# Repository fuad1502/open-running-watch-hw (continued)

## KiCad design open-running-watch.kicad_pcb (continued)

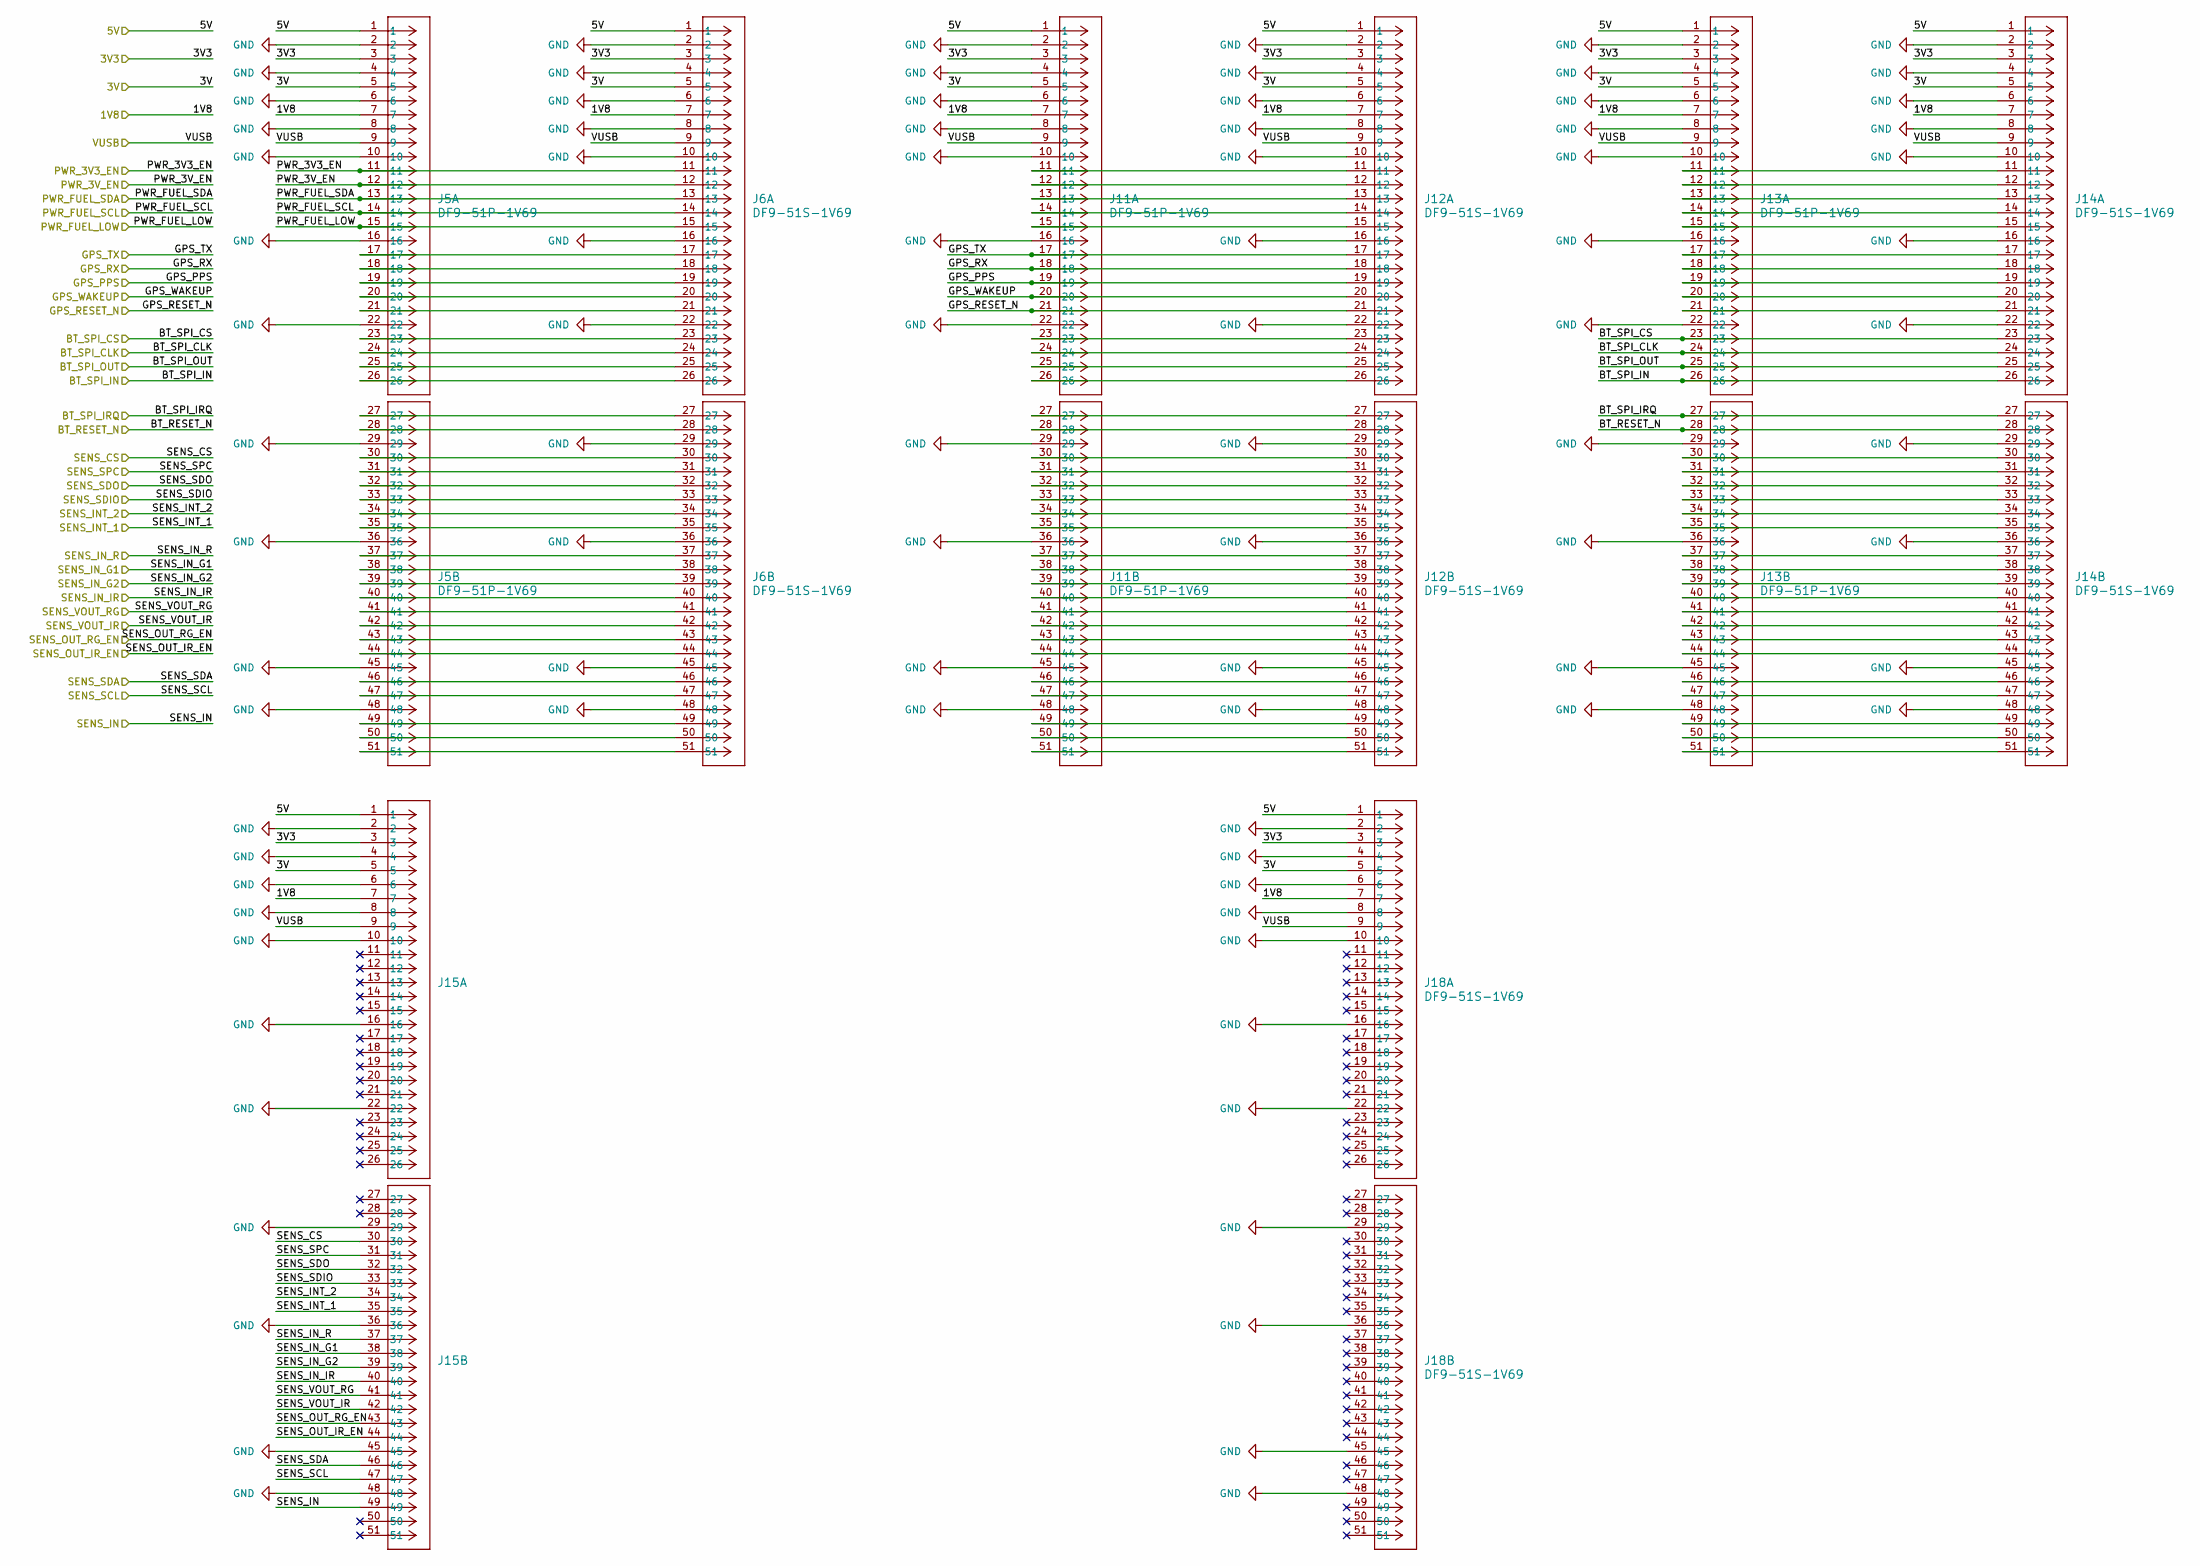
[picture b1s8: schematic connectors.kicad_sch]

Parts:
J5, J11, J13, J15: DF9-51P-1V69; CON9_1X51_MDZL_DF9_HIR
J6, J12, J14, J18: DF9-51S-1V69; CON9_1X51_DZL_DF9_HIR

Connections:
/1V8: J5.7, J6.7, J11.7, J12.7, J13.7, J14.7, J15.7, J18.7; also elsewhere on the board
/3V: J5.5, J6.5, J11.5, J12.5, J13.5, J14.5, J15.5, J18.5; also elsewhere on the board
/3V3: J5.3, J6.3, J11.3, J12.3, J13.3, J14.3, J15.3, J18.3; also elsewhere on the board
/5V: J5.1, J6.1, J11.1, J12.1, J13.1, J14.1, J15.1, J18.1; also elsewhere on the board
/BT_RESET_N: J13.28, J14.28; also elsewhere on the board
/BT_SPI_CLK: J13.24, J14.24; also elsewhere on the board
/BT_SPI_CS: J13.23, J14.23; also elsewhere on the board
/BT_SPI_IN: J13.26, J14.26; also elsewhere on the board
/BT_SPI_IRQ: J13.27, J14.27; also elsewhere on the board
/BT_SPI_OUT: J13.25, J14.25; also elsewhere on the board
/GPS_PPS: J11.19, J12.19; also elsewhere on the board
/GPS_RESET_N: J11.21, J12.21; also elsewhere on the board
/GPS_RX: J11.18, J12.18; also elsewhere on the board
/GPS_TX: J11.17, J12.17; also elsewhere on the board
/GPS_WAKEUP: J11.20, J12.20; also elsewhere on the board
/PWR_3V3_EN: J5.11, J6.11; also elsewhere on the board
/PWR_3V_EN: J5.12, J6.12; also elsewhere on the board
/PWR_FUEL_LOW: J5.15, J6.15; also elsewhere on the board
/PWR_FUEL_SCL: J5.14, J6.14; also elsewhere on the board
/PWR_FUEL_SDA: J5.13, J6.13; also elsewhere on the board
/SENS_CS: J15.30; also elsewhere on the board
/SENS_IN: J15.49; also elsewhere on the board
/SENS_INT_1: J15.35; also elsewhere on the board
/SENS_INT_2: J15.34; also elsewhere on the board
/SENS_IN_G1: J15.38; also elsewhere on the board
/SENS_IN_G2: J15.39; also elsewhere on the board
/SENS_IN_IR: J15.40; also elsewhere on the board
/SENS_IN_R: J15.37; also elsewhere on the board
/SENS_OUT_IR_EN: J15.44; also elsewhere on the board
/SENS_OUT_RG_EN: J15.43; also elsewhere on the board
/SENS_SCL: J15.47; also elsewhere on the board
/SENS_SDA: J15.46; also elsewhere on the board
/SENS_SDIO: J15.33; also elsewhere on the board
/SENS_SDO: J15.32; also elsewhere on the board
/SENS_SPC: J15.31; also elsewhere on the board
/SENS_VOUT_IR: J15.42; also elsewhere on the board
/SENS_VOUT_RG: J15.41; also elsewhere on the board
/VUSB: J5.9, J6.9, J11.9, J12.9, J13.9, J14.9, J15.9, J18.9; also elsewhere on the board
GND: J5.2, J5.4, J5.6, J5.8, J5.10, J5.16, J5.22, J5.29, J5.36, J5.45, J5.48, J6.2, J6.4, J6.6, J6.8, J6.10, J6.16, J6.22, J6.29, J6.36, J6.45, J6.48, J11.2, J11.4, J11.6, J11.8, J11.10, J11.16, J11.22, J11.29, J11.36, J11.45, J11.48, J12.2, J12.4, J12.6, J12.8, J12.10, J12.16, J12.22, J12.29, J12.36, J12.45, J12.48, J13.2, J13.4, J13.6, J13.8, J13.10, J13.16, J13.22, J13.29, J13.36, J13.45, J13.48, J14.2, J14.4, J14.6, J14.8, J14.10, J14.16, J14.22, J14.29, J14.36, J14.45, J14.48, J15.2, J15.4, J15.6, J15.8, J15.10, J15.16, J15.22, J15.29, J15.36, J15.45, J15.48, J18.2, J18.4, J18.6, J18.8, J18.10, J18.16, J18.22, J18.29, J18.36, J18.45, J18.48; also elsewhere on the board
unnamed: J5.17, J6.17
unnamed: J5.18, J6.18
unnamed: J5.19, J6.19
unnamed: J5.20, J6.20
unnamed: J5.21, J6.21
unnamed: J5.23, J6.23
unnamed: J5.24, J6.24
unnamed: J5.25, J6.25
unnamed: J5.26, J6.26
unnamed: J5.27, J6.27
unnamed: J5.28, J6.28
unnamed: J5.30, J6.30
unnamed: J5.31, J6.31
unnamed: J5.32, J6.32
unnamed: J5.33, J6.33
unnamed: J5.34, J6.34
unnamed: J5.35, J6.35
unnamed: J5.37, J6.37
unnamed: J5.38, J6.38
unnamed: J5.39, J6.39
unnamed: J5.40, J6.40
unnamed: J5.41, J6.41
unnamed: J5.42, J6.42
unnamed: J5.43, J6.43
unnamed: J5.44, J6.44
unnamed: J5.46, J6.46
unnamed: J5.47, J6.47
unnamed: J5.49, J6.49
unnamed: J5.50, J6.50
unnamed: J5.51, J6.51
unnamed: J11.11, J12.11
unnamed: J11.12, J12.12
unnamed: J11.13, J12.13
unnamed: J11.14, J12.14
unnamed: J11.15, J12.15
unnamed: J11.23, J12.23
unnamed: J11.24, J12.24
unnamed: J11.25, J12.25
unnamed: J11.26, J12.26
unnamed: J11.27, J12.27
unnamed: J11.28, J12.28
unnamed: J11.30, J12.30
unnamed: J11.31, J12.31
unnamed: J11.32, J12.32
unnamed: J11.33, J12.33
unnamed: J11.34, J12.34
unnamed: J11.35, J12.35
unnamed: J11.37, J12.37
unnamed: J11.38, J12.38
unnamed: J11.39, J12.39
unnamed: J11.40, J12.40
unnamed: J11.41, J12.41
unnamed: J11.42, J12.42
unnamed: J11.43, J12.43
unnamed: J11.44, J12.44
unnamed: J11.46, J12.46
unnamed: J11.47, J12.47
unnamed: J11.49, J12.49
unnamed: J11.50, J12.50
unnamed: J11.51, J12.51
unnamed: J13.11, J14.11
unnamed: J13.12, J14.12
unnamed: J13.13, J14.13
unnamed: J13.14, J14.14
unnamed: J13.15, J14.15
unnamed: J13.17, J14.17
unnamed: J13.18, J14.18
unnamed: J13.19, J14.19
unnamed: J13.20, J14.20
unnamed: J13.21, J14.21
unnamed: J13.30, J14.30
unnamed: J13.31, J14.31
unnamed: J13.32, J14.32
unnamed: J13.33, J14.33
unnamed: J13.34, J14.34
unnamed: J13.35, J14.35
unnamed: J13.37, J14.37
unnamed: J13.38, J14.38
unnamed: J13.39, J14.39
unnamed: J13.40, J14.40
unnamed: J13.41, J14.41
unnamed: J13.42, J14.42
unnamed: J13.43, J14.43
unnamed: J13.44, J14.44
unnamed: J13.46, J14.46
unnamed: J13.47, J14.47
unnamed: J13.49, J14.49
unnamed: J13.50, J14.50
unnamed: J13.51, J14.51

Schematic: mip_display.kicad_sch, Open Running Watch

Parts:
C79, C82, C85, C86: 1u; C_0603_1608Metric; Manufacturer_Part_Number C0603C105K4RACTU
C80, C81: 100n; C_0402_1005Metric; Manufacturer_Part_Number GRM155R71A104MA01D
C84: 560p; C_0402_1005Metric; Manufacturer_Part_Number GRT1555C1H561FA02D
IC21: LSF0204GU12X; Mouser Part Number 771-LSF0204GU12X
J3: 1-2328702-0; 123287020; Mouser Part Number 571-1-2328702-0
J4: 2328702-4; 23287024; Mouser Part Number 571-2328702-4
Q4: BC846; SOT-23; Manufacturer_Part_Number BC847BLT1G
R46: 10k; R_0402_1005Metric; Manufacturer_Part_Number RC0402JR-0710KP
R59, R62: 0; R_0402_1005Metric_Pad0.72x0.64mm_HandSolder; Manufacturer_Part_Number AC0402JR-7D0RL
R60, R61: 0; R_0402_1005Metric_Pad0.72x0.64mm_HandSolder; Manufacturer_Part_Number AC0402JR-7D0RL; not fitted

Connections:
/1V8: C81.2, C82.2, IC21.1 (REFA); also elsewhere on the board
/5V: C85.2, C86.2, J3.4, J3.5; also elsewhere on the board
/controller/CS3_1: IC21.3 (A2); also elsewhere on the board
/controller/DISP_EN: IC21.2 (A1); also elsewhere on the board
/controller/DISP_IO_EN: IC21.12 (EN); also elsewhere on the board
/controller/SPI3_CK: IC21.5 (A4); also elsewhere on the board
/controller/SPI3_MOSI: IC21.4 (A3); also elsewhere on the board
/controller/TIM2_CH1: R46.2; also elsewhere on the board
/mip_display/BL_GND: Q4.3 (C), R59.1, R61.2
/mip_display/DISP_DISP: C84.1, IC21.10 (B1), J3.6
/mip_display/DISP_SCLK: IC21.7 (B4), J3.10
/mip_display/DISP_SCS: IC21.9 (B2), J3.8
/mip_display/DISP_SI: IC21.8 (B3), J3.9
/mip_display/DISP_VDDIO: C79.2, C80.2, IC21.11 (REFB), R60.1, R62.2; also elsewhere on the board
GND: C79.1, C80.1, C81.1, C82.1, C84.2, C85.1, C86.1, IC21.6 (GND), J3.1, J3.2, J3.3, J3.7, Q4.2 (E); also elsewhere on the board
unnamed: J4.1, J4.2, R59.2, R60.2
unnamed: J4.3, J4.4, R61.1, R62.1
unnamed: Q4.1 (B), R46.1

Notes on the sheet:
Level translator
Display interface
Backlight
VBE = 0.7 V Min. hFE = 200 VCE sat. = 0.25 V
Max. current consumption = 25 mA

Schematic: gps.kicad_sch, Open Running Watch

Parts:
ANT2: PCS.55.A; PCS55A; Mouser Part Number 960-PCS.55.A
C16: 2.2p; C_0402_1005Metric; Manufacturer_Part_Number GRM1555C1H2R2CA01D
C17, C18: 100n; C_0402_1005Metric; Manufacturer_Part_Number GRM155R71A104MA01D
C19, C21: 120p; C_0402_1005Metric; Manufacturer_Part_Number GCM1555C1H121JA16D
C20: 1n; C_0402_1005Metric; Manufacturer_Part_Number GCM155R71H102KA37D
FL1: B39162B4327P810; FIL_B39162B4327P810; Manufacturer_Part_Number B39162B4327P810
IC2: TESEO-LIV3F; SON110P970X1010X230-18N; Mouser Part Number 511-TESEO-LIV3F
IC3: BGA_725L6_E6327; BGA725L6E6327; Mouser Part Number 726-BGA725L6E6327
L2: 10n; L_0402_1005Metric; Manufacturer_Part_Number LQG15HS10NH02D
L3: 5.6n; L_0402_1005Metric; Manufacturer_Part_Number LQW15AN5N6G80D
L8: 15n; L_0402_1005Metric; Manufacturer_Part_Number LQG15HN15NG02D
R5: 10k; R_0402_1005Metric; Manufacturer_Part_Number RC0402JR-0710KP

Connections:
/1V8: C17.1, IC2.6 (VBATT); also elsewhere on the board
/GPS_PPS: IC2.4 (1PPS); also elsewhere on the board
/GPS_RESET_N: IC2.9 (SYS_RSTN); also elsewhere on the board
/GPS_RX: IC2.3 (RX); also elsewhere on the board
/GPS_TX: IC2.2 (TX); also elsewhere on the board
/GPS_WAKEUP: IC2.5 (WAKE-UP); also elsewhere on the board
/gps/ANT_IN: C16.2, C21.2, L8.2
/gps/ANT_OFF: IC2.13 (ANT_OFF), IC3.6 (PON), R5.1
/gps/VCC: C18.1, IC2.7 (VCC_IO), IC2.8 (VCC); also elsewhere on the board
/gps/VCC_RF: C20.1, IC2.14 (VCC_RF), IC3.2 (VCC)
GND: ANT2.2 (GROUND), C17.2, C18.2, C20.2, FL1.2 (GND), FL1.3 (GND), FL1.5 (GND), IC2.1 (GND), IC2.10 (GND_RF_1), IC2.12 (GND_RF_2), IC3.1 (GND), IC3.4 (GNDRF), L2.1, L8.1, R5.2; also elsewhere on the board
unnamed: ANT2.1 (RF_FEED), C16.1, L2.2
unnamed: C21.1, L3.2
unnamed: C19.2, FL1.1 (INPUT)
unnamed: FL1.4 (OUTPUT), IC3.3 (AO)
unnamed: C19.1, IC2.11 (RF_IN)
unnamed: IC3.5 (AI), L3.1

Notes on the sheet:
Peak current 44.4 mA Typ.

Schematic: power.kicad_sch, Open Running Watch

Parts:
BT1: Battery; SolderWire-0.1sqmm_1x02_P3.6mm_D0.4mm_OD1mm
C22, C23, C24, C25: 1u; C_0603_1608Metric; Manufacturer_Part_Number C0603C105K4RACTU
C26, C27, C28, C31, C63: 4.7u; C_0402_1005Metric; Manufacturer_Part_Number GRM155R60J475ME87J
C29, C30: 2.2u; C_0402_1005Metric; Manufacturer_Part_Number GRM155R60J225ME95J
C64, C65, C66: 10u; C_0603_1608Metric; Manufacturer_Part_Number GRM188R60J106ME47J
IC4: BQ27441DRZR-G1A; BQ27441DRZRG1A; Mouser Part Number 595-BQ27441DRZR-G1A
IC5: MCP73811T-420I_OT; SOT95P270X145-5N; Mouser Part Number 579-MCP73811T-420IOT
IC6: TPS62237DRYR; Texas_USON-6_1x1.45mm_P0.5mm_SMD; Mouser Part Number 595-TPS62237DRYR
IC7: ST1S15J18R; BGA6C40P2X3_94X119X60; Mouser Part Number 511-ST1S15J18R
IC13: TPS613222ADBVR; SOT95P280X145-5N; Mouser Part Number 595-TPS613222ADBVR
L4, L5: 1u; L_1008_2520Metric; Manufacturer_Part_Number LQM2HPN1R0MJ0L
L6: 470n; L_0805_2012Metric; Manufacturer_Part_Number LQM21PNR47MC0D
L7: 2.2u; L_1008_2520Metric; Manufacturer_Part_Number DFE252012F-2R2M=P2
R6: 10m; R_1206_3216Metric; Manufacturer_Part_Number CRF1206-FZ-R010ELF
R7: 2k; R_0402_1005Metric; Manufacturer_Part_Number RC0402FR-132KL
R8, R10, R11: 10k; R_0402_1005Metric; Manufacturer_Part_Number RC0402JR-0710KP
R9: 1M; R_0402_1005Metric; Manufacturer_Part_Number RC0402JR-071ML
U1: TPS62233DRYR; Texas_USON-6_1x1.45mm_P0.5mm_SMD; Manufacturer_Part_Number TPS62233DRYR

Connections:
/1V8: C31.2, IC7.C1 (FB), L6.2; also elsewhere on the board
/3V: C26.1, L5.1, U1.6 (FB); also elsewhere on the board
/3V3: C27.1, IC6.6 (FB), L4.1; also elsewhere on the board
/5V: C64.2, C65.2, C66.2, IC13.4 (VOUT); also elsewhere on the board
/PWR_3V3_EN: IC6.5 (EN), R11.1; also elsewhere on the board
/PWR_3V_EN: R10.1, U1.5 (EN); also elsewhere on the board
/PWR_FUEL_LOW: IC4.12 (GPOUT); also elsewhere on the board
/PWR_FUEL_SCL: IC4.2 (SCL); also elsewhere on the board
/PWR_FUEL_SDA: IC4.1 (SDA); also elsewhere on the board
/VUSB: C25.1, IC5.1 (CE), IC5.4 (VDD); also elsewhere on the board
/power/SRN: C24.1, C28.2, C29.1, C30.1, C63.2, IC4.7 (SRN), IC5.3 (VBAT), IC6.3 (VIN), IC7.A2 (VIN), L7.1, R6.2, R9.1, R10.2, R11.2, U1.3 (VIN)
/power/SRP: BT1.1 (+), C22.1, IC4.6 (BAT), IC4.8 (SRP), R6.1
GND: BT1.2 (-), C22.2, C23.2, C24.2, C25.2, C26.2, C27.2, C28.1, C29.2, C30.2, C31.1, C63.1, C64.1, C65.1, C66.1, IC4.3 (VSS), IC4.13 (EP), IC5.2 (VSS), IC6.1 (MODE), IC6.4 (GND), IC7.A1 (MODE), IC7.C2 (GND), IC13.2 (GND), R7.2, R8.1, U1.1 (MODE), U1.4 (GND); also elsewhere on the board
unnamed: IC4.10 (BIN), R8.2
unnamed: C23.1, IC4.5 (VDD)
unnamed: IC5.5 (PROG), R7.1
unnamed: IC6.2 (SW), L4.2
unnamed: IC7.B2 (EN), R9.2
unnamed: IC7.B1 (SW), L6.1
unnamed: IC13.1 (SW), L7.2
unnamed: L5.2, U1.2 (SW)

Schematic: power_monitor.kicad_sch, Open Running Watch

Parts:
C72: 100n; C_0402_1005Metric; Manufacturer_Part_Number GRM155R71A104MA01D
IC14: INA186A5IYFDR; BGA6C40P3X2_117X76X40; Mouser Part Number 595-INA186A5IYFDR
R34: 10m; R_1206_3216Metric; Manufacturer_Part_Number CRF1206-FZ-R010ELF
R35: 10k; R_0402_1005Metric; Manufacturer_Part_Number RC0402JR-0710KP
R36: 0; R_0402_1005Metric_Pad0.72x0.64mm_HandSolder; Manufacturer_Part_Number AC0402JR-7D0RL; not fitted
TP1: 5029; Mouser Part Number 534-5029; not fitted

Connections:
/3V3_FLASH: C72.2, IC14.A1 (IN+), IC14.A2 (VS), R34.1, R35.1; also elsewhere on the board
/controller/VCC_FLASH: IC14.B1 (IN-), R34.2; also elsewhere on the board
/controller/power_monitor/OUT: IC14.A3 (OUT), TP1.1 (1_1)
GND: C72.1, IC14.B2 (GND), R36.2; also elsewhere on the board
unnamed: IC14.B3 (ENABLE), R35.2, R36.1

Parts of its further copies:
C73, C74, C75, C77, C78, C83: 100n; C_0402_1005Metric; Manufacturer_Part_Number GRM155R71A104MA01D
IC15, IC16, IC17, IC19, IC20, IC22: INA186A5IYFDR; BGA6C40P3X2_117X76X40; Mouser Part Number 595-INA186A5IYFDR
R37, R40, R43, R50, R53, R56: 10m; R_1206_3216Metric; Manufacturer_Part_Number CRF1206-FZ-R010ELF
R38, R41, R44, R51, R54, R57: 10k; R_0402_1005Metric; Manufacturer_Part_Number RC0402JR-0710KP
R39, R42, R45, R52, R55, R58: 0; R_0402_1005Metric_Pad0.72x0.64mm_HandSolder; Manufacturer_Part_Number AC0402JR-7D0RL; not fitted
TP2, TP3, TP4, TP6, TP7, TP8: 5029; Mouser Part Number 534-5029; not fitted

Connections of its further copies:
/1V8: C73.2, C74.2, C75.2, IC15.A1 (IN+), IC15.A2 (VS), IC16.A1 (IN+), IC16.A2 (VS), IC17.A1 (IN+), IC17.A2 (VS), R37.1, R38.1, R40.1, R41.1, R43.1, R44.1; also elsewhere on the board
/3V: C77.2, C83.2, IC19.A1 (IN+), IC19.A2 (VS), IC22.A1 (IN+), IC22.A2 (VS), R50.1, R51.1, R56.1, R57.1; also elsewhere on the board
/3V3: C78.2, IC20.A1 (IN+), IC20.A2 (VS), R53.1, R54.1; also elsewhere on the board
/audio/VCC: IC19.B1 (IN-), R50.2; also elsewhere on the board
/audio/power_monitor5/OUT: IC19.A3 (OUT), TP6.1 (1_1)
/biometric/VCC: IC20.B1 (IN-), R53.2; also elsewhere on the board
/biometric/power_monitor6/OUT: IC20.A3 (OUT), TP7.1 (1_1)
/bluenrg/VBAT: IC17.B1 (IN-), R43.2; also elsewhere on the board
/bluenrg/power_monitor3/OUT: IC17.A3 (OUT), TP4.1 (1_1)
/controller/VDD: IC15.B1 (IN-), R37.2; also elsewhere on the board
/controller/power_monitor1/OUT: IC15.A3 (OUT), TP2.1 (1_1)
/gps/VCC: IC16.B1 (IN-), R40.2; also elsewhere on the board
/gps/power_monitor2/OUT: IC16.A3 (OUT), TP3.1 (1_1)
/mip_display/DISP_VDDIO: IC22.B1 (IN-), R56.2; also elsewhere on the board
/mip_display/power_monitor7/OUT: IC22.A3 (OUT), TP8.1 (1_1)
GND: C73.1, C74.1, C75.1, C77.1, C78.1, C83.1, IC15.B2 (GND), IC16.B2 (GND), IC17.B2 (GND), IC19.B2 (GND), IC20.B2 (GND), IC22.B2 (GND), R39.2, R42.2, R45.2, R52.2, R55.2, R58.2; also elsewhere on the board
unnamed: IC15.B3 (ENABLE), R38.2, R39.1
unnamed: IC16.B3 (ENABLE), R41.2, R42.1
unnamed: IC17.B3 (ENABLE), R44.2, R45.1
unnamed: IC19.B3 (ENABLE), R51.2, R52.1
unnamed: IC20.B3 (ENABLE), R54.2, R55.1
unnamed: IC22.B3 (ENABLE), R57.2, R58.1

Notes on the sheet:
5 mV/mA

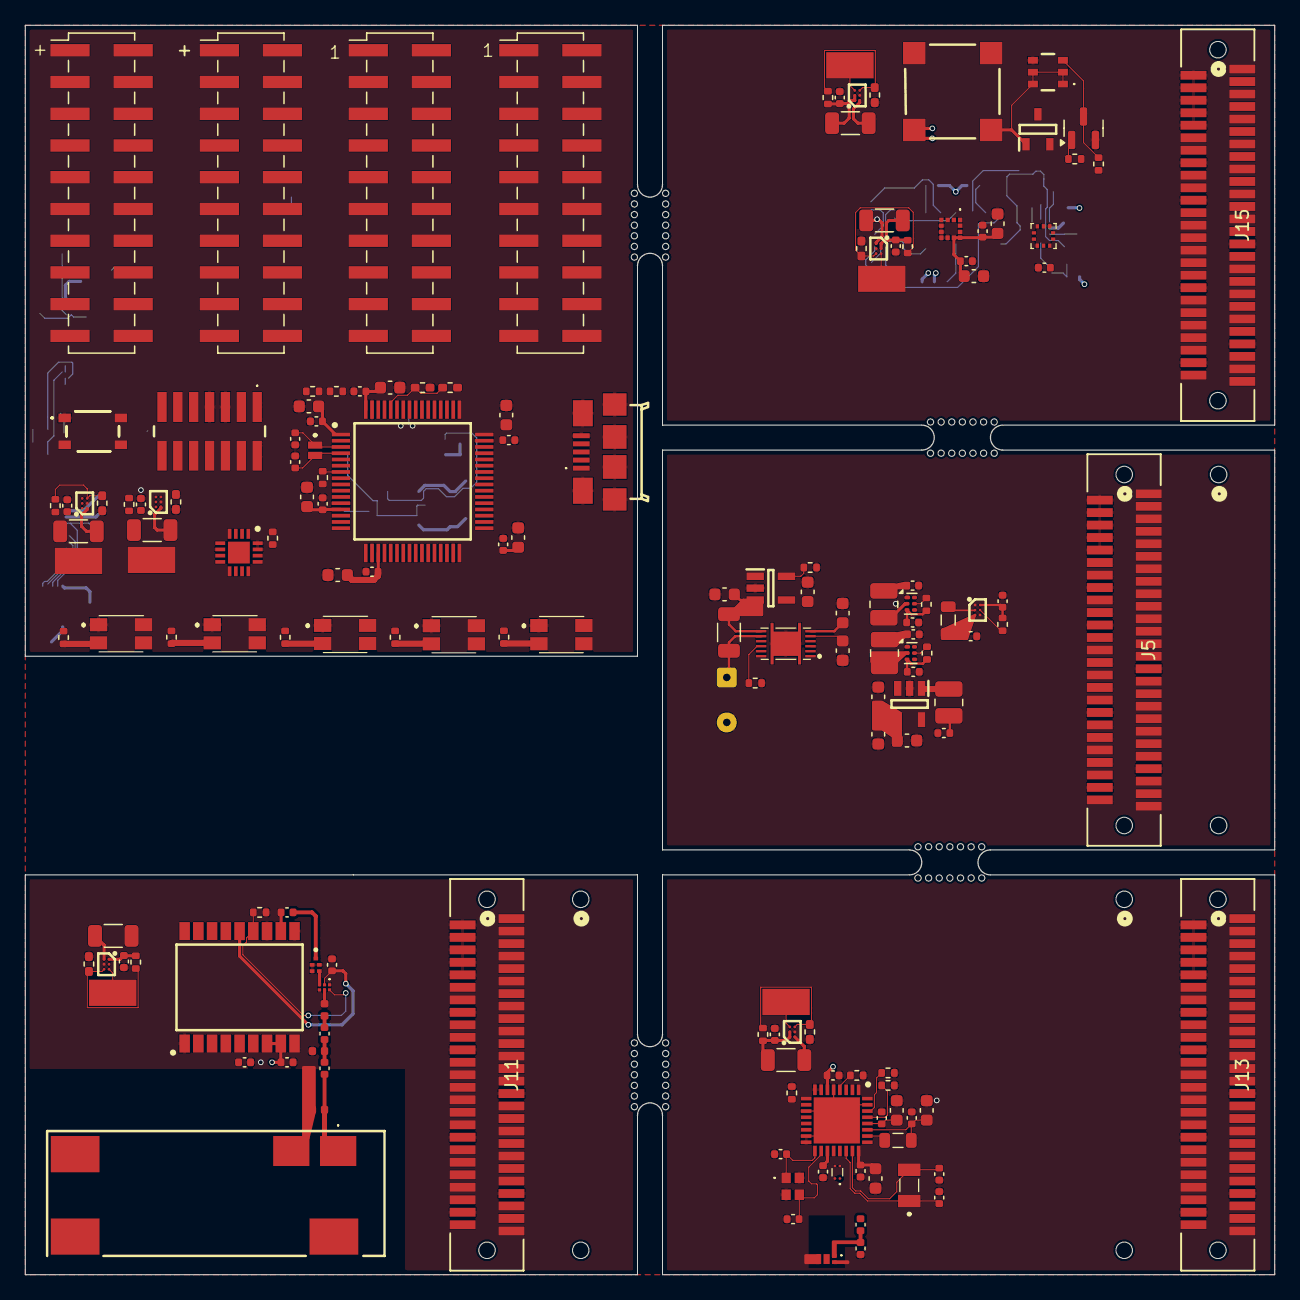
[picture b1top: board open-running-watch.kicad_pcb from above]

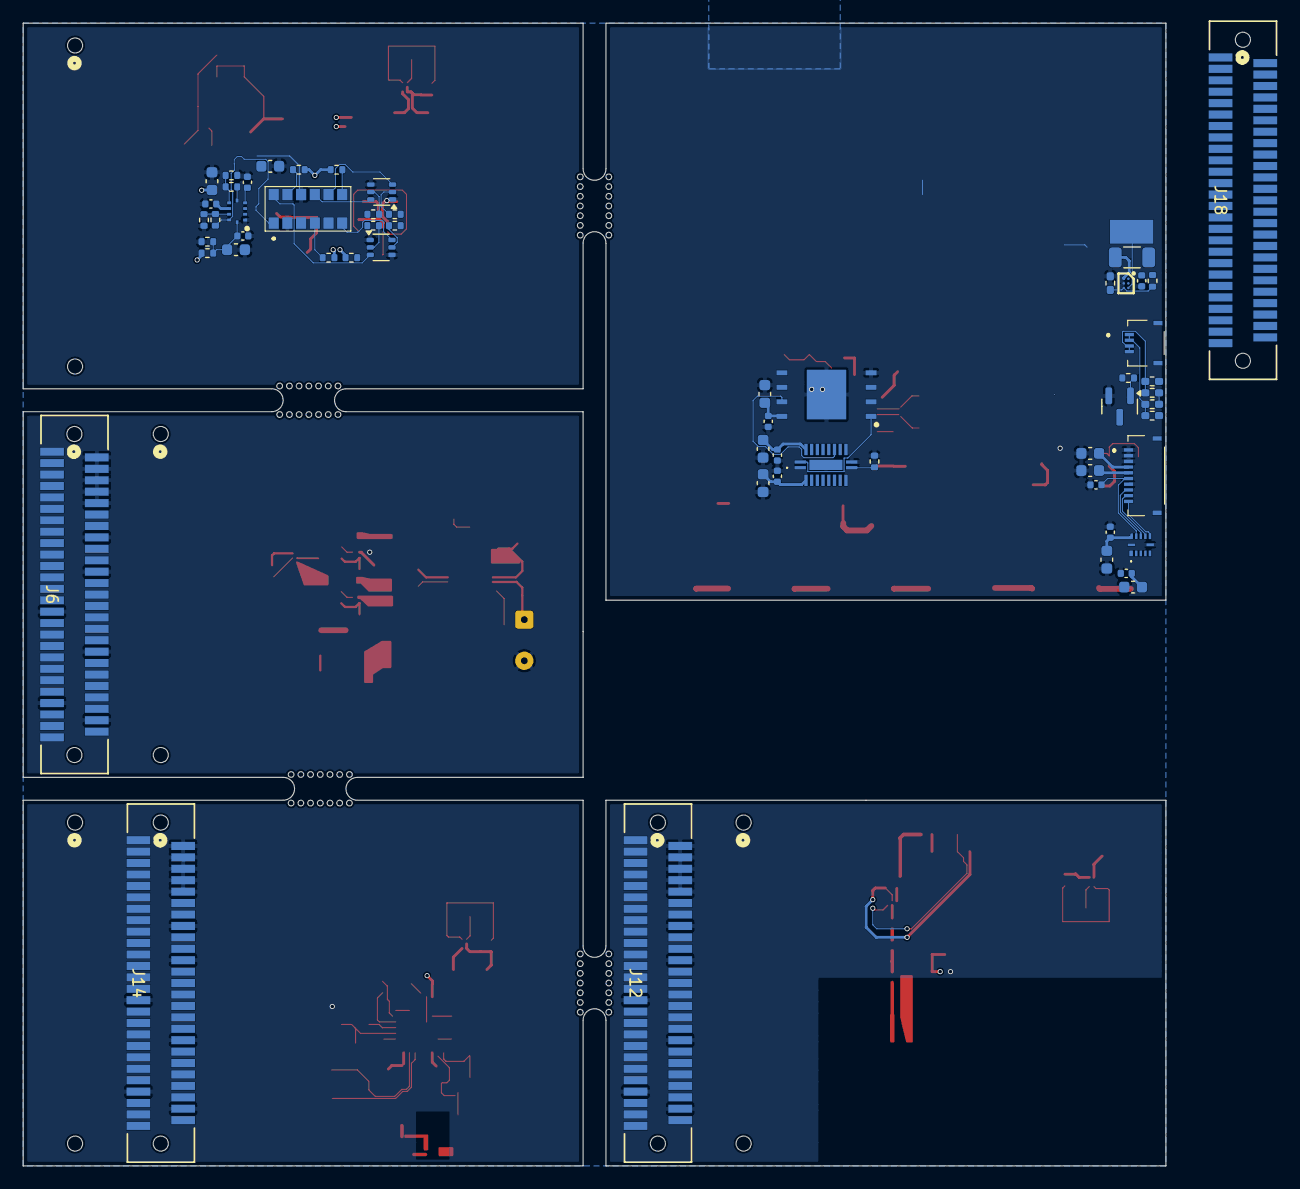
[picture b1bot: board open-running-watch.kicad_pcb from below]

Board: 4 copper layers, 100.0 x 100.0 mm, 221 parts (59 on the bottom side), 268 nets.

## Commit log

2024-04-12 Initial commit: finished first pass of schematic; Still need to resolve unconnected pins; Added all models
2024-04-12 Add company name (using github URL), date, and change revision number to all schematic pages
2024-04-13 Changed display to 12616-06 Sharp MIP display with Azumo backlight
2024-04-13 Add 5V boost switching regulator
2024-04-13 Changed to smaller tactile switch
2024-04-13 Changed hand soldered footprints to normal footprints
2024-04-14 Setup technology stackup and rules
2024-04-14 Changed GNSS antenna matching to world wide setting
2024-04-14 Add RF and Power net classes to schematic nets
2024-04-14 Place all components to PCB; Defined board layout
2024-04-16 Create symbol and footprint for the display to guide display interface placement
2024-04-16 Changed regulator footprint to KiCad provided one
2024-04-16 Remove BOOT0 switch to 0 ohm resistors
2024-04-16 Remove RF netclass from a net in gps sheet; Monitor DISP_VDDIO instead of DISP_VDD; Correct constraints
2024-04-16 Finished component placement and component grouping wirings
2024-04-17 Finished hardware design
2024-04-17 Remove additional spaces in Manufacturer_Part_Number field
2024-04-17 Add NC to IO expander pins
2024-04-17 Pulled in symbol attribute changes from schematic to PCB
2024-04-17 Changed battery connection footprint
2024-04-17 Add fabrication output generation automation
2024-04-17 Add GitHub workflow
2024-04-17 Change GitHub CI to use KiCad 8 container
2024-04-17 Trigger GitHub action on release instead
2024-04-17 Changed tag pattern detect in GitHub action trigger
2024-04-17 Fixed workflow typo
2024-04-17 Use personal access token in secrets instead
2024-04-17 Add images
2024-04-17 Add images to README, and modified some text.
2024-05-03 Added 'sponsored by PCBWay' silkscreen
2024-05-13 Newline added at the end of all schematics due to newer KiCad/Ubuntu version
2024-05-13 Added NMOS transistor to models
2024-05-13 Changed transistor used in display backlight switch
2024-05-13 Use NPN NMOS pair to switch the piezo on and off, to support higher current handling
2024-05-13 Connect photodetector cathode instead of anode to amplifier input
2024-05-13 Add pull up to IO expander reset input; Corrected MISO/MOSI connection to hierarchical pin; Made USB data line as a differential line
2024-05-13 Bumped schematic version to 0.1.1 and updated issue date
2024-05-13 Updated PCB to reflect schematic changes since v0.1.0
2024-05-13 Bumped PCB version number to 0.1.1 and updated issue date
2024-05-13 Set 'do not populate' on power monitor probe point
2024-05-13 Create an opening in the bottom plane solder mask to allow connection to ground
2024-05-13 Narrow down solder mask opening and just position to minimize risk of electrical short
2024-05-13 Change version to 0.2.1; The previous release should've increased the minor version number
2024-05-13 Reflect DNP in schematic to PCB
2024-05-13 Bump version to v0.2.2
2026-05-17 Upgrade to KiCad 10
2026-05-17 Add .history and .lck files to .gitignore
2026-05-25 TEMP COMMIT
